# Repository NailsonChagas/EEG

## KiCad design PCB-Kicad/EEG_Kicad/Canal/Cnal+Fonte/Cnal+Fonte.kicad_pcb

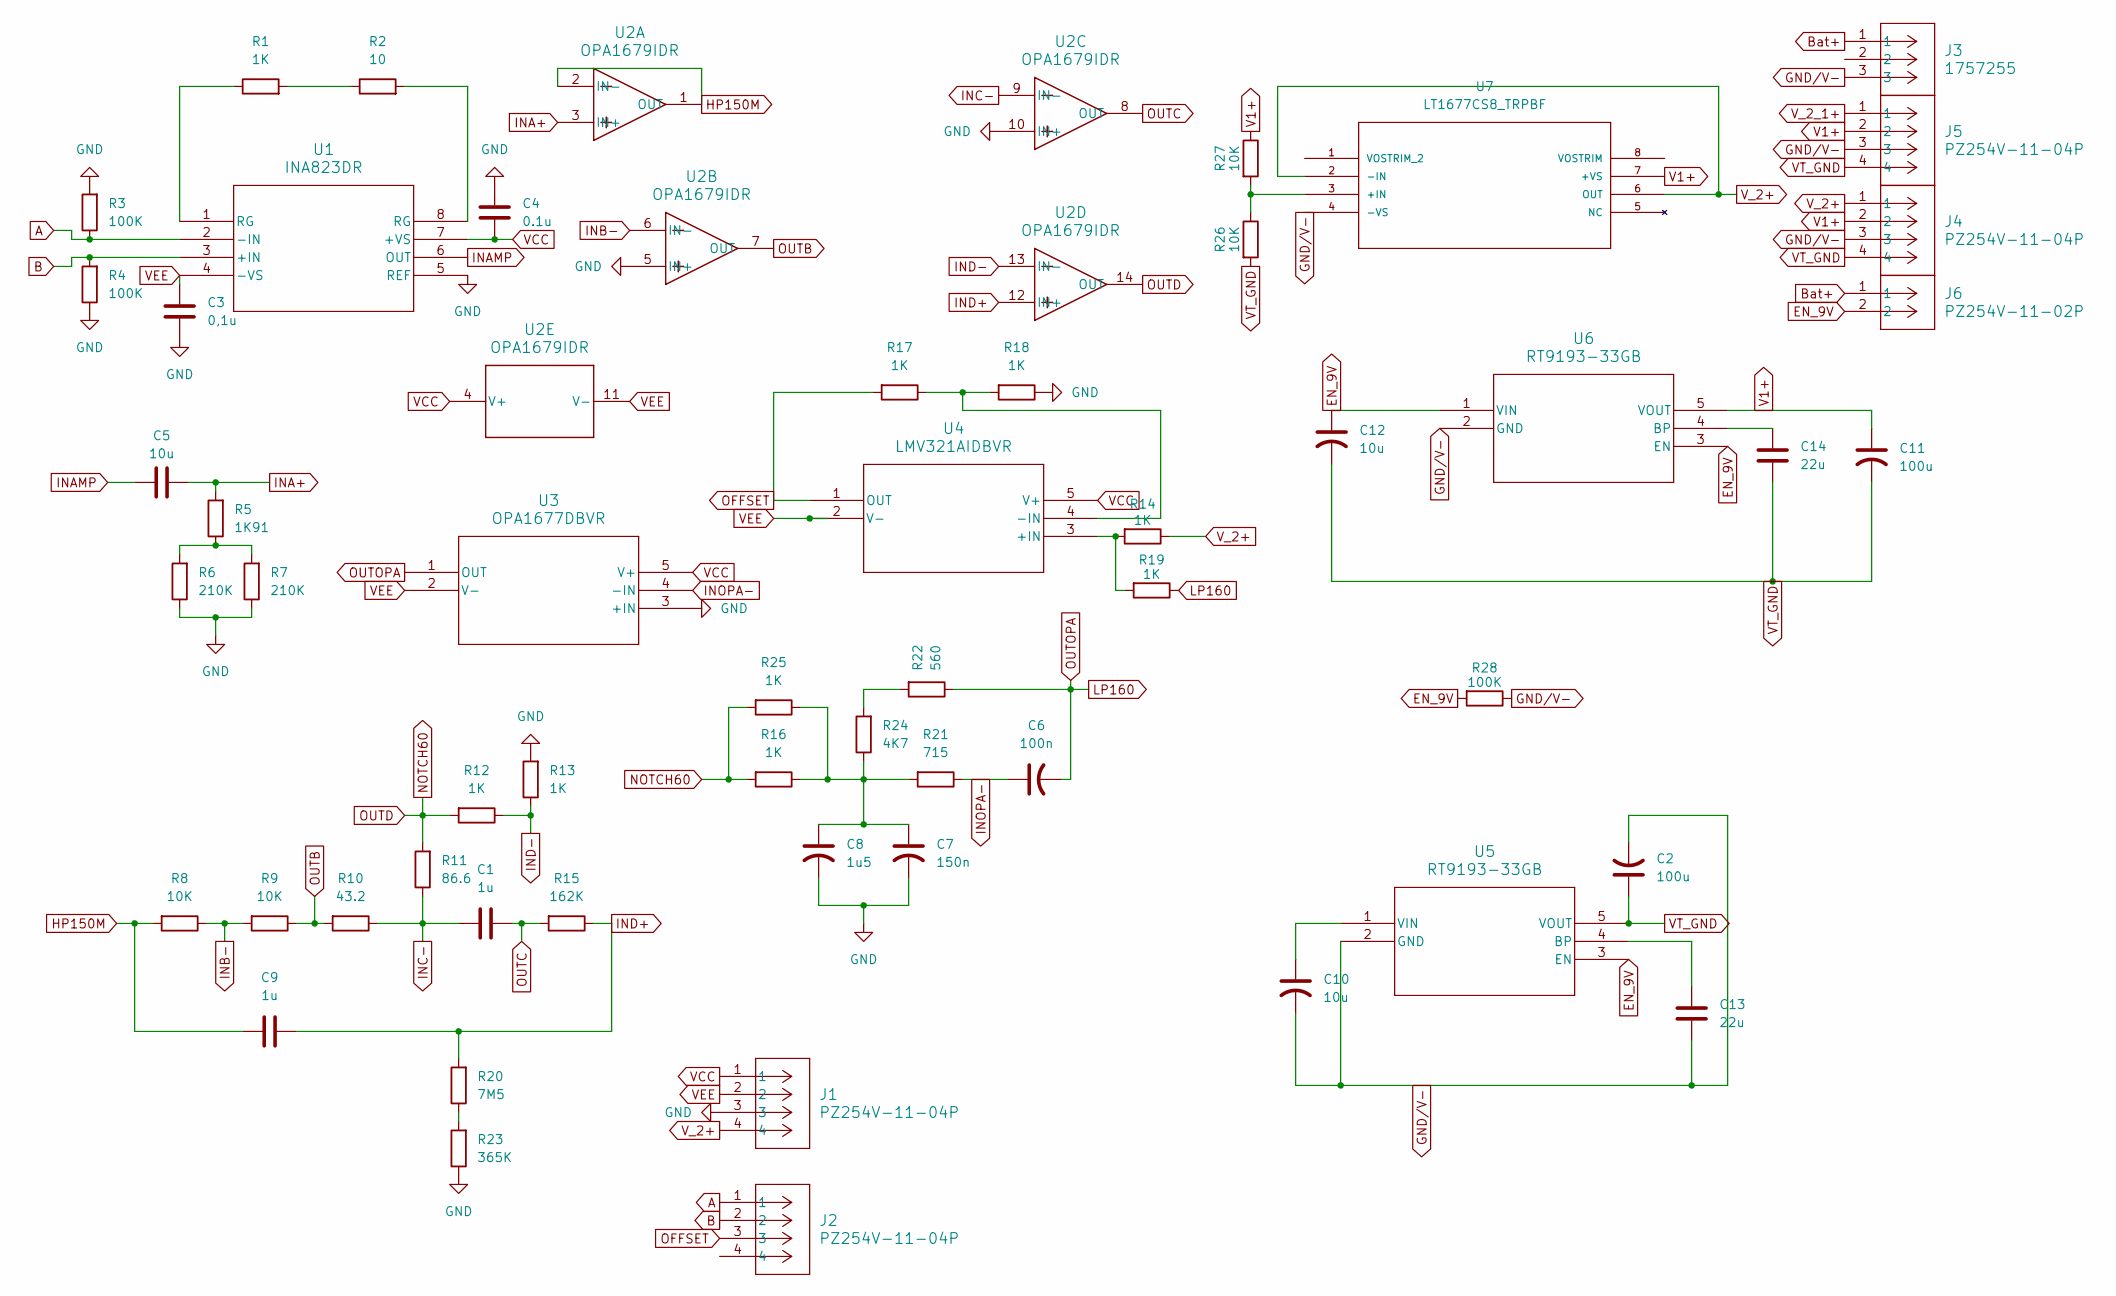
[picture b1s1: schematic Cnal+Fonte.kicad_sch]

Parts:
C1, C9: 1u; C_Axial_L5.1mm_D3.1mm_P7.50mm_Horizontal
C2, C11: 100u; C_Disc_D3.0mm_W1.6mm_P2.50mm
C3: 0,1u; CP_Radial_D10.0mm_P5.00mm
C4: 0.1u; CP_Radial_D10.0mm_P5.00mm
C5: 10u; CP_Radial_D10.0mm_P5.00mm
C6: 100n; C_Disc_D3.0mm_W1.6mm_P2.50mm
C7: 150n; C_Axial_L5.1mm_D3.1mm_P7.50mm_Horizontal
C8: 1u5; C_Axial_L5.1mm_D3.1mm_P7.50mm_Horizontal
C10, C12: 10u; C_Disc_D3.0mm_W1.6mm_P2.50mm
C13, C14: 22u; C_Axial_L5.1mm_D3.1mm_P7.50mm_Horizontal
J1, J2, J4, J5: PZ254V-11-04P; CONN_PZ254V-11-04P_XFC
J3: 1757255; CONN_1757255_PXC
J6: PZ254V-11-02P; CONN_PZ254V-11-02P_02P_XFC
R1, R12, R13, R14, R16, R17, R18, R19, R25: 1K; R_Axial_DIN0207_L6.3mm_D2.5mm_P10.16mm_Horizontal
R2: 10; R_Axial_DIN0207_L6.3mm_D2.5mm_P10.16mm_Horizontal
R3, R4, R28: 100K; R_Axial_DIN0207_L6.3mm_D2.5mm_P10.16mm_Horizontal
R5: 1K91; R_Axial_DIN0207_L6.3mm_D2.5mm_P10.16mm_Horizontal
R6, R7: 210K; R_Axial_DIN0207_L6.3mm_D2.5mm_P10.16mm_Horizontal
R8, R9, R26, R27: 10K; R_Axial_DIN0207_L6.3mm_D2.5mm_P10.16mm_Horizontal
R10: 43.2; R_Axial_DIN0207_L6.3mm_D2.5mm_P10.16mm_Horizontal
R11: 86.6; R_Axial_DIN0207_L6.3mm_D2.5mm_P10.16mm_Horizontal
R15: 162K; R_Axial_DIN0207_L6.3mm_D2.5mm_P10.16mm_Horizontal
R20: 7M5; R_Axial_DIN0207_L6.3mm_D2.5mm_P10.16mm_Horizontal
R21: 715; R_Axial_DIN0207_L6.3mm_D2.5mm_P10.16mm_Horizontal
R22: 560; R_Axial_DIN0207_L6.3mm_D2.5mm_P10.16mm_Horizontal
R23: 365K; R_Axial_DIN0207_L6.3mm_D2.5mm_P10.16mm_Horizontal
R24: 4K7; R_Axial_DIN0207_L6.3mm_D2.5mm_P10.16mm_Horizontal
U1: INA823DR; D0008A_SOIC_TEX
U2: OPA1679IDR; D0014A_N
U3: OPA1677DBVR; SOT23_DBV0005A_TEX
U4: LMV321AIDBVR; DBV5_TEX
U5, U6: RT9193-33GB; SOT-23-5_RIT
U7: LT1677CS8_TRPBF; SO-8_S; MANUFACTURER_PART_NUMBER lt1677cs8

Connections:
A: J2.1, R3.1, U1.2 (-IN)
B: J2.2, R4.2, U1.3 (+IN)
Bat+: J3.1, J6.1
EN_9V: C12.1, J6.2, R28.2, U5.3 (EN), U6.1 (VIN), U6.3 (EN)
GND: C3.2, C4.1, C7.2, C8.2, J1.3, R3.2, R4.1, R6.1, R7.1, R13.2, R18.1, R23.1, U1.5 (REF), U2.5 (IN+), U2.10 (IN+), U3.3 (+IN)
GND/V-: C2.2, C10.2, C13.2, J3.3, J4.3, J5.3, R28.1, U5.2 (GND), U6.2 (GND), U7.4 (-VS)
HP150M: C9.2, R8.2, U2.1 (OUT), U2.2 (IN-)
INA+: C5.2, R5.2, U2.3 (IN+)
INAMP: C5.1, U1.6 (OUT)
INB-: R8.1, R9.2, U2.6 (IN-)
INC-: C1.2, R10.1, R11.1, U2.9 (IN-)
IND+: C9.1, R15.1, R20.2, U2.12 (IN+)
IND-: R12.1, R13.1, U2.13 (IN-)
INOPA-: C6.1, R21.1, U3.4 (-IN)
LP160: C6.2, R19.1, R22.1, U3.1 (OUT)
NOTCH60: R11.2, R12.2, R16.2, R25.2, U2.14 (OUT)
unnamed: C7.1, C8.1, R16.1, R21.2, R24.1, R25.1
unnamed: R1.1, U1.1 (RG)
unnamed: R1.2, R2.1
unnamed: R2.2, U1.8 (RG)
unnamed: R5.1, R6.2, R7.2
unnamed: R20.1, R23.2
unnamed: R22.2, R24.2
unnamed: R14.2, R19.2, U4.3 (+IN)
unnamed: R17.1, R18.2, U4.4 (-IN)
unnamed: C13.1, U5.4 (BP)
unnamed: C10.1, U5.1 (VIN)
unnamed: C14.1, U6.4 (BP)
unnamed: R26.1, R27.2, U7.3 (+IN)
OFFSET: J2.3, R17.2, U4.1 (OUT)
OUTB: R9.1, R10.2, U2.7 (OUT)
OUTC: C1.1, R15.2, U2.8 (OUT)
V1+: C11.1, J4.2, J5.2, R27.1, U6.5 (VOUT), U7.7 (+VS)
VCC: C4.2, J1.1, U1.7 (+VS), U2.4 (V+), U3.5 (V+), U4.5 (V+)
VEE: C3.1, J1.2, U1.4 (-VS), U2.11 (V-), U3.2 (V-), U4.2 (V-)
VT_GND: C2.1, C11.2, C12.2, C14.2, J4.4, J5.4, R26.2, U5.5 (VOUT)

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
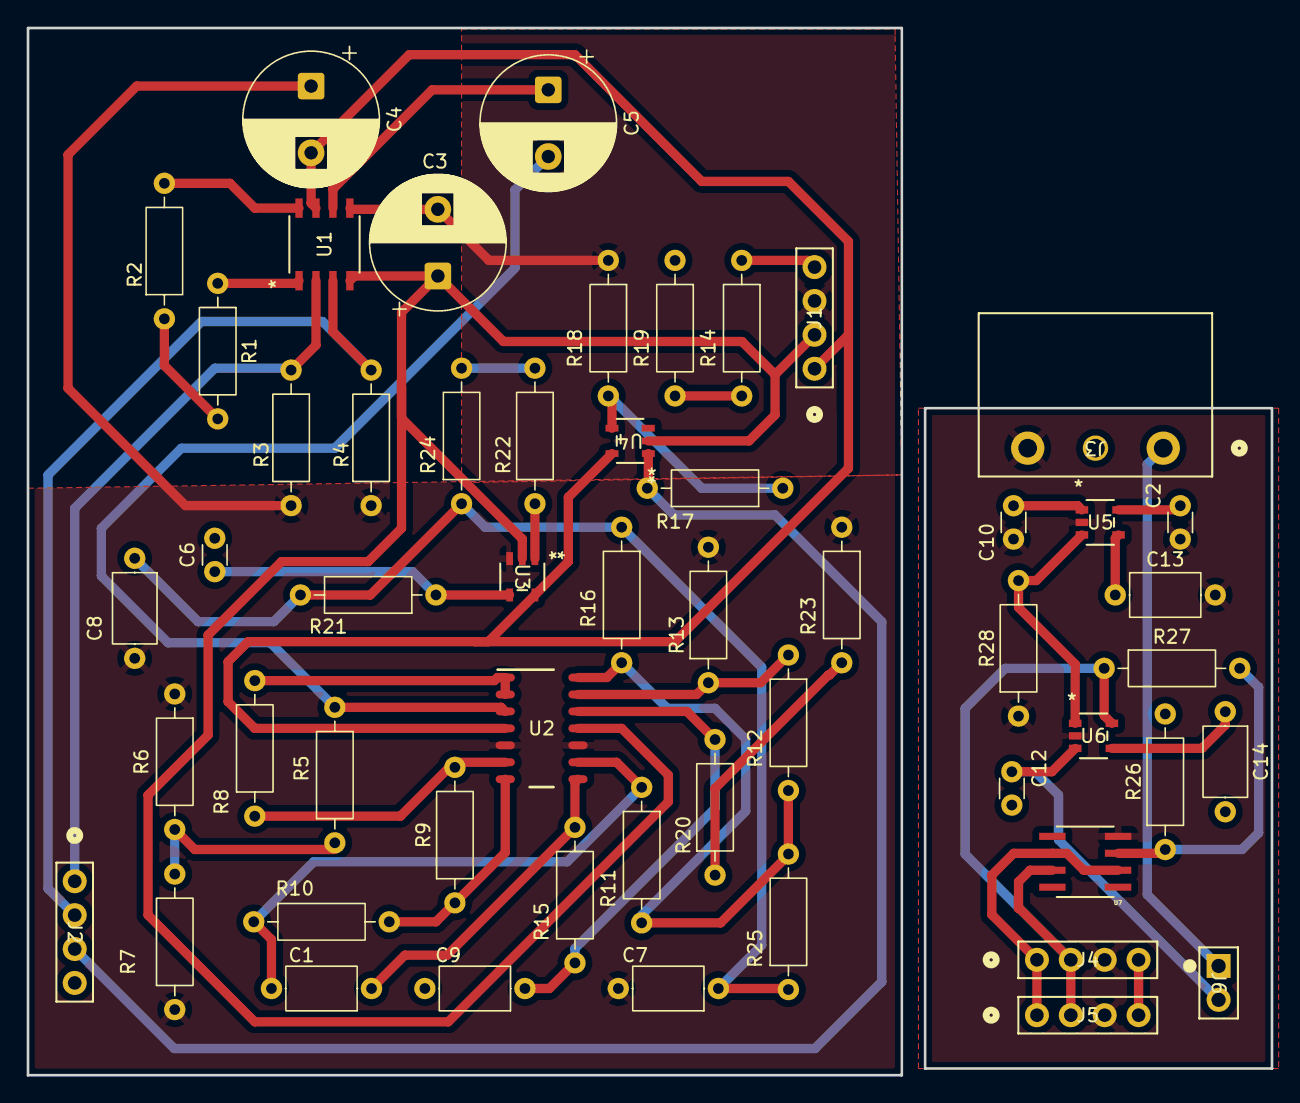
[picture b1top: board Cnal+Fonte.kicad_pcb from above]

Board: 2 copper layers, 93.2 x 78.5 mm, 54 parts (0 on the bottom side), 38 nets.

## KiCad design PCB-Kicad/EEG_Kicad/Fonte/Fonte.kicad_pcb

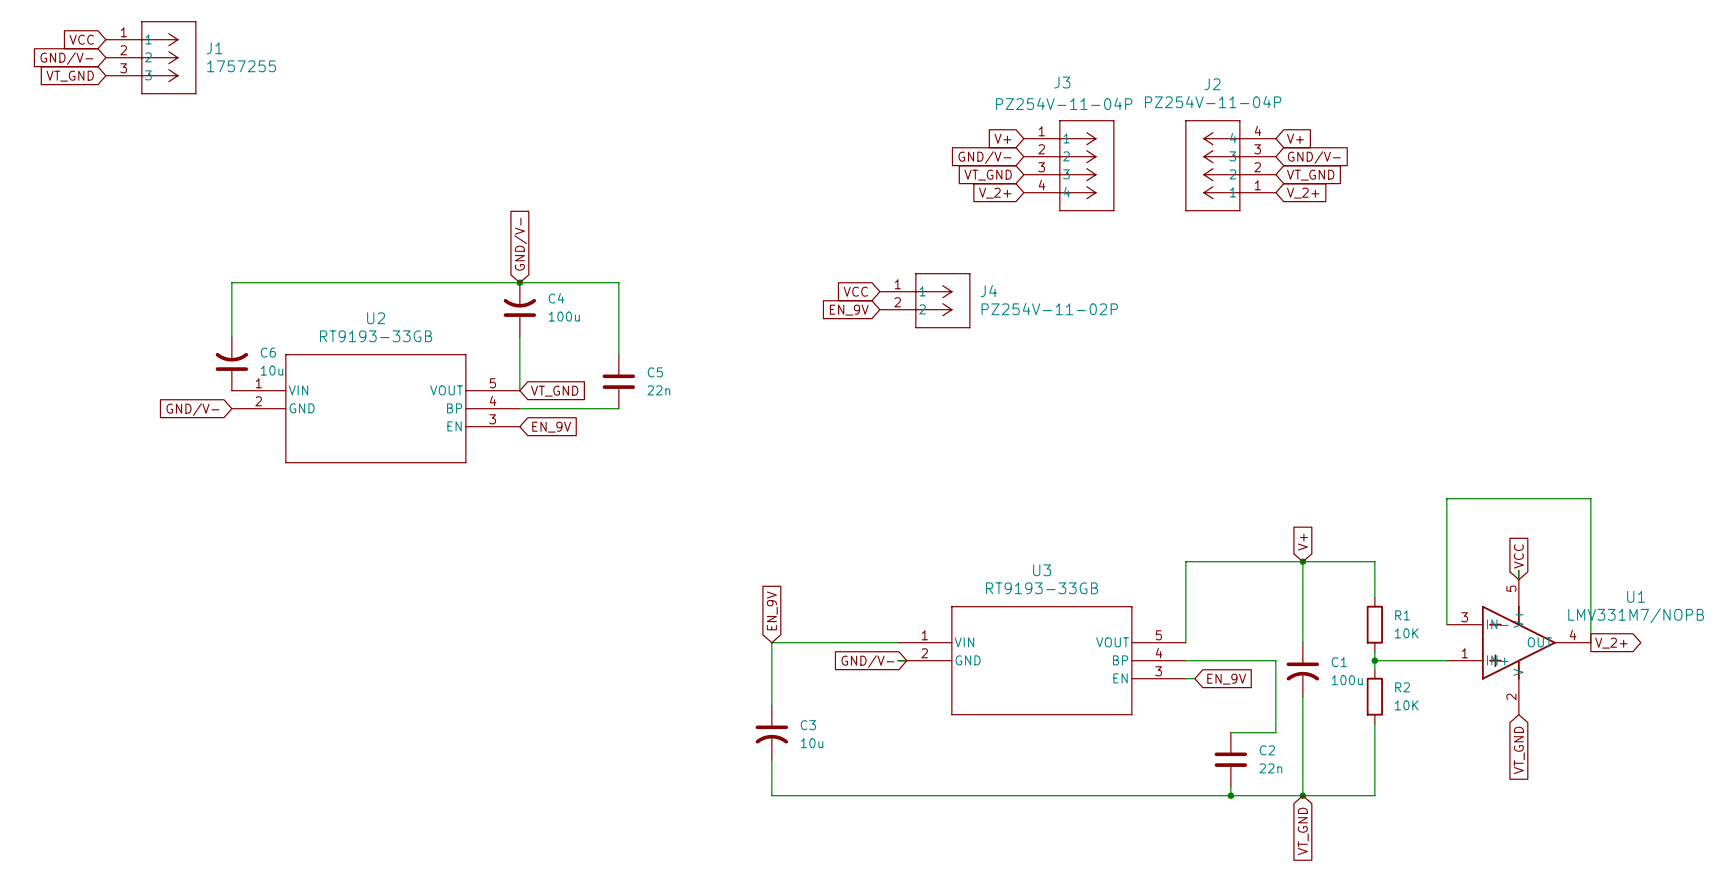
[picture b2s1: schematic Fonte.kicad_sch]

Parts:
C1, C4: 100u; CP_Radial_D5.0mm_P2.50mm
C2, C5: 22n; C_Disc_D3.0mm_W2.0mm_P2.50mm
C3, C6: 10u; CP_Radial_D5.0mm_P2.50mm
J1: 1757255; CONN_1757255_PXC
J2, J3: PZ254V-11-04P; CONN_PZ254V-11-04P_XFC
J4: PZ254V-11-02P; CONN_PZ254V-11-02P_02P_XFC
R1, R2: 10K; R_Axial_DIN0207_L6.3mm_D2.5mm_P10.16mm_Horizontal
U1: LMV331M7/NOPB; MAA05A
U2, U3: RT9193-33GB; SOT-23-5_RIT

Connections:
EN_9V: C3.1, J4.2, U2.3 (EN), U3.1 (VIN), U3.3 (EN)
GND/V-: C4.2, C5.1, C6.2, J1.2, J2.3, J3.2, U2.2 (GND), U3.2 (GND)
unnamed: R1.2, R2.1, U1.1 (IN+)
unnamed: C5.2, U2.4 (BP)
unnamed: C6.1, U2.1 (VIN)
unnamed: C2.1, U3.4 (BP)
V+: C1.1, J2.4, J3.1, R1.1, U3.5 (VOUT)
VCC: J1.1, J4.1, U1.5 (V+)
VT_GND: C1.2, C2.2, C3.2, C4.1, J1.3, J2.2, J3.3, R2.2, U1.2 (V-), U2.5 (VOUT)
V_2+: J2.1, J3.4, U1.3 (IN-), U1.4 (OUT)

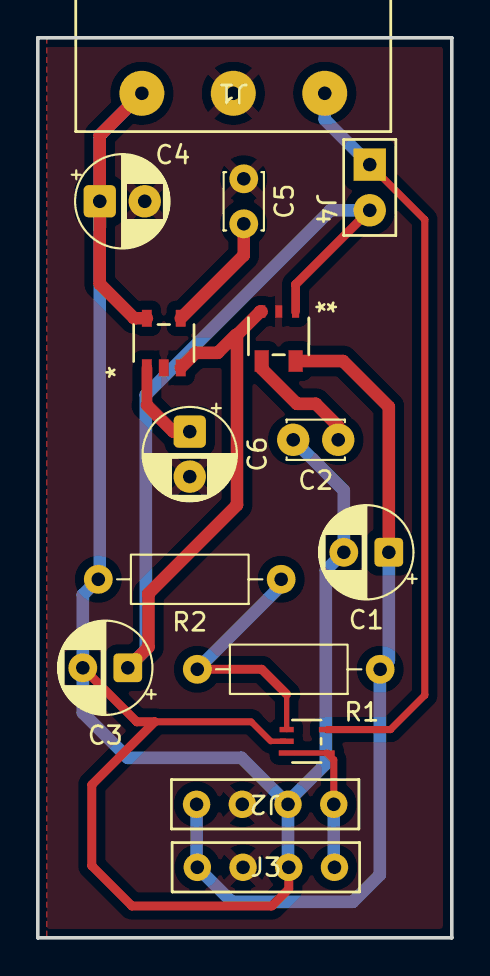
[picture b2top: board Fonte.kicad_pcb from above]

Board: 2 copper layers, 23.0 x 50.0 mm, 15 parts (0 on the bottom side), 10 nets.

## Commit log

2025-04-06 feat: adicionando os modelos dos amplificadores de instrumentação que estamos estudando se podemos usar no desenvolviemnto do canal
2025-04-16 feat: simulando
2025-04-16 feat: calculando a diferença entre os o Vout calculado e o Vout simulado
2025-04-16 feat: colocando os requirimentos para executar o script python
2025-04-30 feat: filtro 60hz
2025-05-05 filtro de 60Hz
2025-05-07 dev canal
2025-05-14 feat: filtro 160Hz
2025-06-04 feat: canal
2025-06-04 amplificador
2025-06-12 feat: eliminando o amplificador
2025-06-12 feat: filtro de quarto grau
2025-06-13 feat: canal do eeg
2025-07-21 feat: fonte simétrica
2025-07-22 feat: fonte simetrica
2025-07-22 feat: removendo componentes não usados e arrumando caminhos absolutos
2025-07-22 removido
2025-07-24 feat: fonte funcionado, falta o divisor de tensão
2025-09-01 feat: correção da fonte
2025-09-02 feat: inserindo comentário na fonte
2025-09-02 feat: diagrama do projeto
2025-09-09 feat: procura do micro
2025-09-09 feat: separando as pastas e fazendo lista de materiais
2025-09-09 remove: arquivos da simulação
2025-09-09 organizando
2025-09-09 feat
2025-09-09 micro
2025-09-11 feat: começcando testar altenarnativas ao LT1112
2025-09-15 feat: substituindo amp op usados nos filtros
2025-09-15 feat: testes dos amp ops
2025-09-16 feat: trocando amp op do offset, falta o da fonte
2025-09-18 feat: atualizando lista de materiais
2025-09-22 feat: terminando a fonte
2025-09-22 feat: lmv321a
2025-09-22 fonte
2025-10-27 feat: começando a programamr o micro
2025-10-27 update event
2025-10-27 lendo em loop
2025-10-27 checkpoint: o dois AD estão sendo lidos
2025-10-28 feat: implementação dos filtros falta aplicar conforme os dados chegam
2025-10-28 feat: integrando filtros
2025-10-28 format
2025-11-03 feat: enviando dados
2025-11-04 feat: plot em tempo real dos canais, falta a conversão para o valor real
2025-11-04 corrigindo eixos
2025-11-04 feat: nome da classe estava errado
2025-11-05 feat: seleção da porta serial
2025-11-05 feat: organizando o código de plot
2025-11-05 feat: criando o readme
2025-11-05 feat: colocando um tamanho minimo na janela
2025-11-05 fix: atualizando arquivo requisitos e adicionando um tratamento para caso n ache dispositivos seriais
2025-11-06 feat: mudando a ordem para organizar
2025-11-06 feat: atualizando versão do stm32cudeIDE
2025-11-06 fix: plot
2025-11-06 feat: filtro passa baixa feito pelo robert
2025-11-06 atualizando readme
2025-11-10 feat: alterando baud rate
2025-11-17 feat: leitura do botão que irá ser responsavel por fazer entrar/sair de low power mode
2025-11-17 feat: modos de baixo consumo
2025-11-17 feat: como valor é trocado dentro de uma interrupção deve ser volatile
2025-12-08 feat: imagens slide
